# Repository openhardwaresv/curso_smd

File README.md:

Sensorino - Iniciandote con Componentes de Montaje Superficial
================================================================

Sensorino es una tableta electrónica programable compatible con
Arduino Leonardo impulsada por la comunidad OpenHardware.SV diseñada
en colaboración por TeUbi.co y ALSW para enseñar los fundamentos
básicos sobre el diseño de tabletas electrónicas haciendo uso de
componentes de montaje superficial.

La tableta es basada en el microcontrolador ATMega32u4 y contiene
el bootloader de Leonardo, pero además incluye sensores y LEDs
indicadores por lo que no requiere de componentes externos más que
una fuente de alimentación una vez programada.

Actualmente la tableta tiene la posibilidad de armarse utilizando el
sensor de gestos APDS-9960 o el inclinómetro sencillo RPI-1031. Estos
sensores permiten implementar aplicaciones muy sencillas que pueden
fácilmente ser demostradas con LEDs incluídos.

Al estar basada en Leonardo la tableta también permite utilizarse como
dispositivo de entrada (teclado o mouse) con lo que se le pueden dar
aplicaciones sumamente interesantes de interacción con computador.

Esta es una tableta didáctica diseñada con la idea de aprender las bases
del diseño utilizando componentes de montaje superficial por lo que se
incluye el mismo diseño eléctrico y de PCB en distintas etapas del
diseño que facilitan y sirven como guía de los productos esperados.

Últimas adiciones
=================

+ Agregado esquemá eléctrico

Costo/Lista de Materiales
=========================

Revisar archivo adjunto BOM.csv.

Pre-requisitos/Requerimientos
=============================

En función del diseño que quieras modificar puedes encontrar las fuentes
en distintas etapas. Sin embargo para seguir todo el proceso desde cero
necesitas cumplir los siguientes requerimientos:

Software:

* EAGLE Layout editor.
* IDE Arduino.
* GIT (para guardar tus avances)

Herramientas requeridas:

* Pistola de calor de temperatura y flujo regulable (Se recomienda Sparkfun 303D)
* Tercera mano
* Pinza curvada auto-blocante anti-estática
* Espátula plástica o tarjeta de vinil (para aplicar la pasta)
* Pasta para soldar libre de plomo

Construcción y uso
==================

Revisar directorio "Documentación"

Carpetas
========
* *doc*: Utiliza esta carpeta para ingresar toda la documentación que consideres
necesaria para tu proyecto. De preferencia utiliza formatos libres como "ODF"
o simples archivos de texto, si puedes crear una página web en HTML recuerda
renombrar el archivo principal como "index.html" para que pueda ser accedido
fácilmente en caso de que alguien copie esta carpeta en un servidor web.
* *src*: Coloca en esta carpeta todos los archivos de código fuente del software
de control de tu proyecto Open Hardware. Si utilizas un IDE como Eclipse o Arduino
copia dentro de src la carpeta del proyecto.
* *dsn* / *diseño*: En esta carpeta coloca todos los archivos para el diseño de tu
proyecto.
  +  *main*: Coloca en esta carpeta los archivos de diseño original que pueden
incluir, pero no limitarse a: Dibujos 2D, diseños 3D, archivos CAD, bibliotecas
de componentes, dibujos técnicos adicionales.
  +  *aux*: Coloca en esta carpeta los archivos de diseño auxiliares que ayuden
a construir tu proyecto. Los archivos de diseño secundario pueden incluír diseños
2D o 3D en formato de intercambio, dibujos técnicos adicionales, formatos listos
para manufactura, artes gráficos adicionales.
* *extra*: Esta carpeta es libre, aquí puedes colocar otros archivos que se
puedan requerir para hacer funcionar o construir tu proyecto. Un ejemplo de ello
puede ser un driver controlador de un dispositivo específico o vínculos a software
relevante, fotografías o videos.

Excepción de responsabilidades
==============================

Es recomendable que incluyas un texto como el siguiente en tus proyectos:

> El presente proyecto se comparte "tal cual" con el único objetivo de que sea útil.
El/los creadores del presente hardware y su software asociado no pueden garantizar su
correcto funcionamiento bajo ninguna circunstancia. El/Los autor/es de este proyecto
no podrá/n hacerse responsable/s de cualquier pérdida de carácter material, personal o
económico a su persona o terceros derivados de la utilización del mismo. Este proyecto
no deberá ser utilizado bajo ninguna circustancia en sistemas de carácter crítico
o sistemas de los cuales dependan vidas de personas de manera directa o indirecta.

Licenciamiento
==============

Agrega aquí la licencia que utilizas en el código fuente de tu proyecto, adicionalmente
agradeceríamos si colocas la nota de atribución de la plantilla al final.

> La plantilla de este README.md ha sido desarrollada por la comunidad openhardware.sv
con el objetivo de facilitar la documentación de proyectos. Esta plantilla está protegida
bajo la licencia CC BY, puedes modificarla y redistribuirla manteniendo esta nota de

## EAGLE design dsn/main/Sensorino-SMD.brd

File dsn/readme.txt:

Archivos de diseño
==================

Encuentra los archivos de diseño de Sensorino en esta carpeta.

Archivos de diseño principal:

* main\Sensorino.sch : Archivo fuente del diagráma eléctrico para Eagle.
* main\Sensorino.brd : Archivo fuente de la tableta impresa para Eagle.

Archivos de diseño auxiliar:
* main\Sensorino_sch_print.pdf : PDF para impresión del diagrama eléctrico
* main\PAD_COMBINADO.jpg : Pad combinado para ambos sensores.

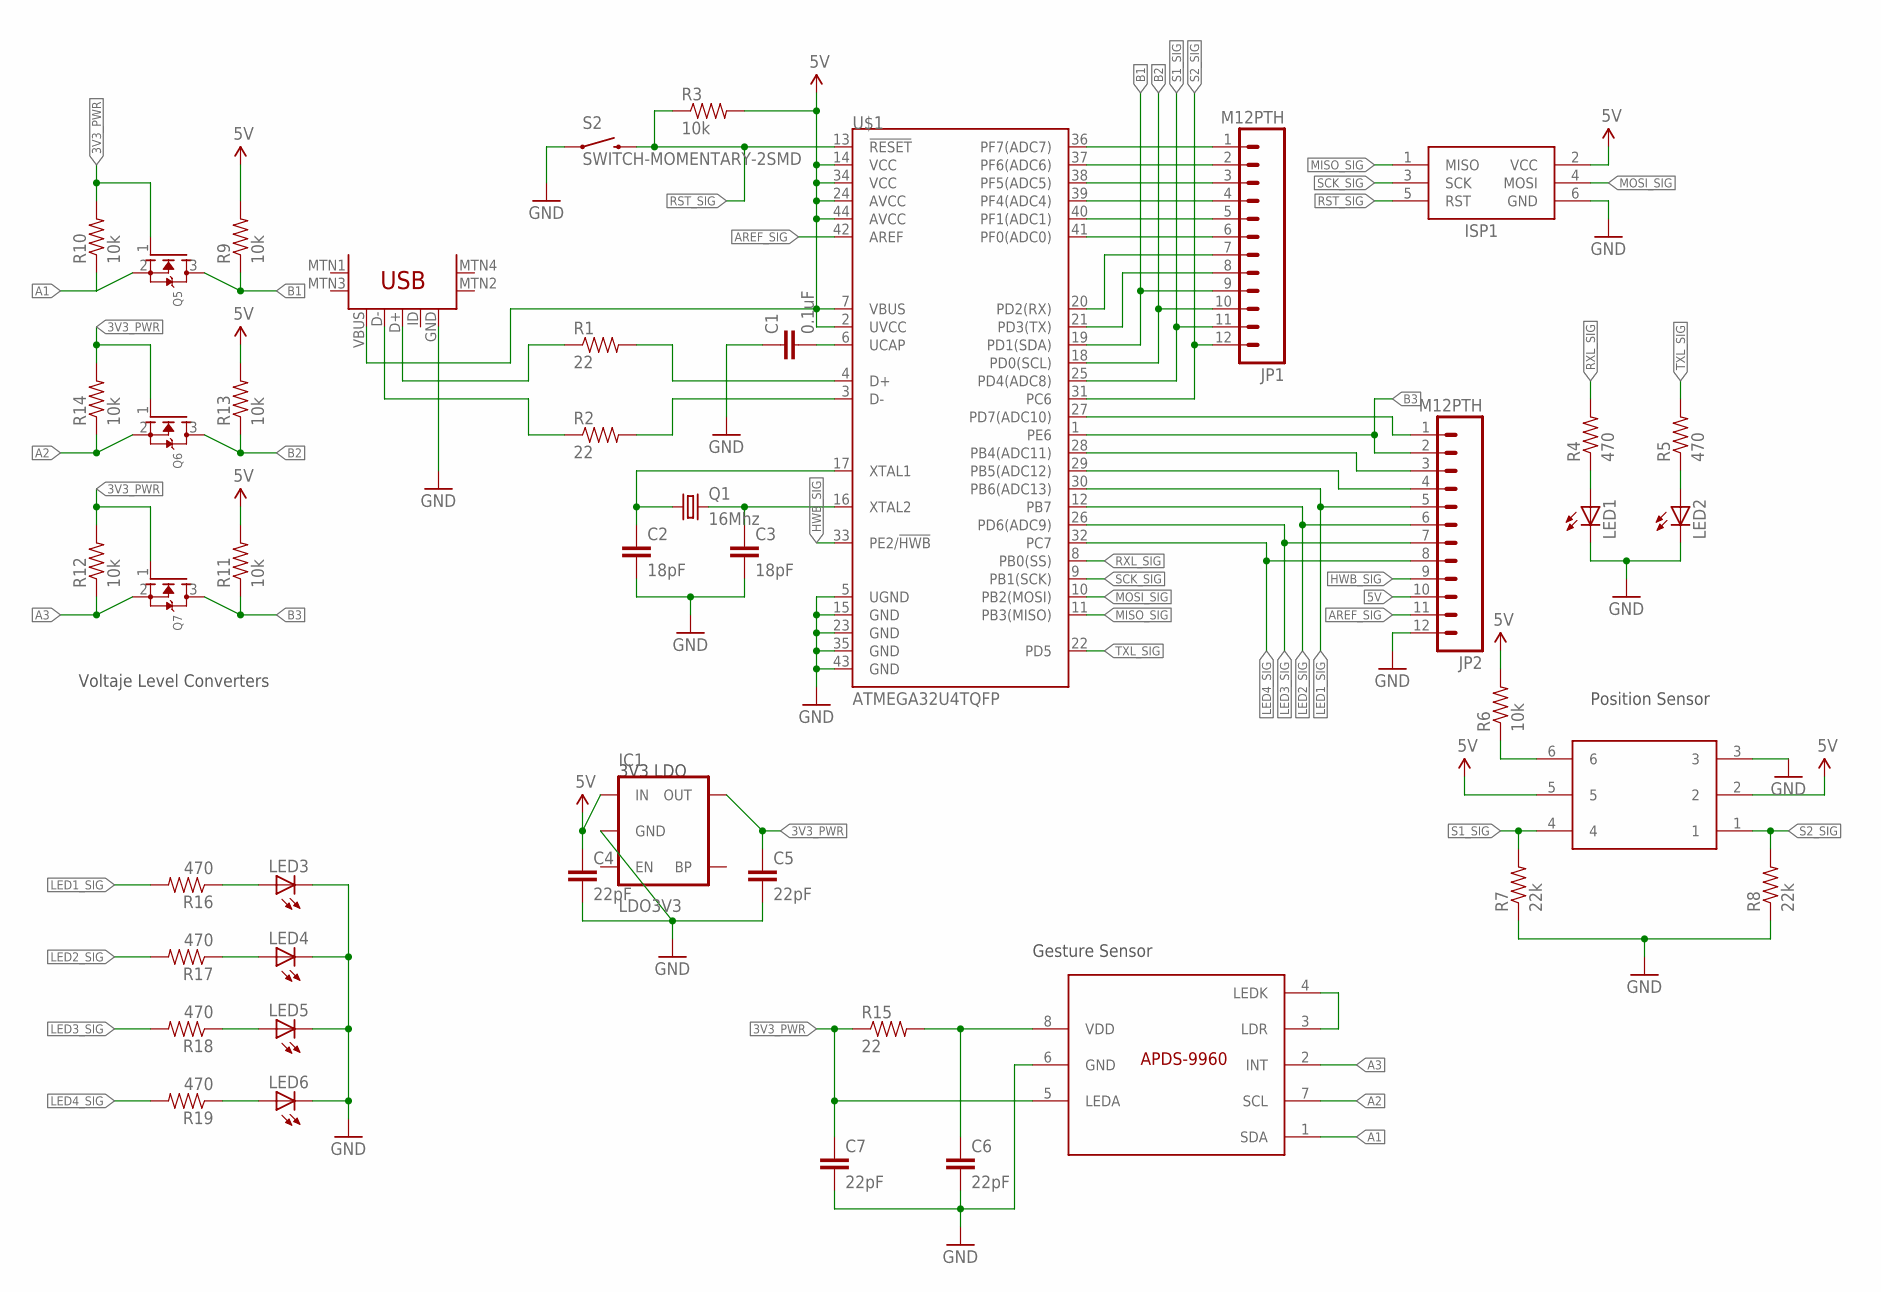
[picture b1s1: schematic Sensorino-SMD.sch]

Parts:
C1: 0.1uF; 0805
C2, C3: 18pF; 0805
C4, C5, C6, C7: 22pF; 0805
IC1: LDO3V3; SOT23-5
ISP1: AVRISP-6; AVRISP
JP1, JP2: M12PTH; 1X12
LED1, LED2, LED3, LED4, LED5, LED6: LED-WHITE; LED-1206
Q1: 16Mhz; CTS406
Q5, Q6, Q7: MOSFET-NREFLOW; SOT23
R1, R2, R15: 22; 0805
R3, R6, R9, R10, R11, R12, R13, R14: 10k; 0805
R4, R5, R16, R17, R18, R19: 470; 0805
R7, R8: 22k; 0805
S2: SWITCH-MOMENTARY-2SMD; TACTILE_SWITCH_SMD
U$1: ATMEGA32U4TQFP; SPARKFUN-DIGITALIC_TQFP44
U$2: USB-MINIB-5PIN; USB-MINIB
U$3: RPI-1031
U$4: APDS-9960

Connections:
3V3_PWR: C5.1, C7.1, IC1.5 (OUT), Q5.1 (G), Q6.1 (G), Q7.1 (G), R10.2, R12.2, R14.2, R15.1, U$4.5 (LEDA)
5V: C4.1, IC1.1 (IN), ISP1.2 (VCC), JP2.10, R3.2, R6.2, R9.2, R11.2, R13.2, U$1.2 (UVCC), U$1.7 (VBUS), U$1.14 (VCC), U$1.24 (AVCC), U$1.34 (VCC), U$1.44 (AVCC), U$2.VBUS, U$3.2, U$3.5
A1: Q5.2 (S), R10.1, U$4.1 (SDA)
A2: Q6.2 (S), R14.1, U$4.7 (SCL)
A3: Q7.2 (S), R12.1, U$4.2 (INT)
AREF_SIG: JP2.11, U$1.42 (AREF)
B1: JP1.9, Q5.3 (D), R9.1, U$1.19 (PD1(SDA))
B2: JP1.10, Q6.3 (D), R13.1, U$1.18 (PD0(SCL))
B3: JP2.2, Q7.3 (D), R11.1, U$1.1 (PE6)
D_USBD+: R2.1, U$2.D-
D_USBD-: R1.1, U$2.D+
D_USBRD+: R2.2, U$1.3 (D-)
D_USBRD-: R1.2, U$1.4 (D+)
GND: C1.1, C2.2, C3.2, C4.2, C5.2, C6.2, C7.2, IC1.2 (GND), ISP1.6 (GND), JP2.12, LED1.C, LED2.C, LED3.C, LED4.C, LED5.C, LED6.C, R7.1, R8.1, S2.1, U$1.5 (UGND), U$1.15 (GND), U$1.23 (GND), U$1.35 (GND), U$1.43 (GND), U$2.GND, U$3.3, U$4.6 (GND)
HWB_SIG: JP2.9, U$1.33 (PE2/!HWB)
LED1_SIG: JP2.5, R16.2, U$1.30 (PB6(ADC13))
LED2_SIG: JP2.6, R17.2, U$1.12 (PB7)
LED3_SIG: JP2.7, R18.2, U$1.26 (PD6(ADC9))
LED4_SIG: JP2.8, R19.2, U$1.32 (PC7)
MISO_SIG: ISP1.1 (MISO), U$1.11 (PB3(MISO))
MOSI_SIG: ISP1.4 (MOSI), U$1.10 (PB2(MOSI))
unnamed: JP2.1, U$1.27 (PD7(ADC10))
unnamed: C1.2, U$1.6 (UCAP)
unnamed: C3.1, Q1.3 (2), U$1.16 (XTAL2)
unnamed: C2.1, Q1.1, U$1.17 (XTAL1)
unnamed: LED3.A, R16.1
unnamed: JP2.3, U$1.28 (PB4(ADC11))
unnamed: LED1.A, R4.1
unnamed: LED2.A, R5.1
unnamed: JP1.1, U$1.36 (PF7(ADC7))
unnamed: JP1.2, U$1.37 (PF6(ADC6))
unnamed: JP1.3, U$1.38 (PF5(ADC5))
unnamed: JP1.4, U$1.39 (PF4(ADC4))
unnamed: JP1.5, U$1.40 (PF1(ADC1))
unnamed: JP1.6, U$1.41 (PF0(ADC0))
unnamed: JP1.7, U$1.20 (PD2(RX))
unnamed: JP1.8, U$1.21 (PD3(TX))
unnamed: LED4.A, R17.1
unnamed: LED5.A, R18.1
unnamed: LED6.A, R19.1
unnamed: JP2.4, U$1.29 (PB5(ADC12))
unnamed: R6.1, U$3.6
unnamed: U$4.3 (LDR), U$4.4 (LEDK)
unnamed: C6.1, R15.2, U$4.8 (VDD)
RST_SIG: ISP1.5 (RST), R3.1, S2.3 (2), U$1.13 (!RESET)
RXL_SIG: R4.2, U$1.8 (PB0(SS))
S1_SIG: JP1.11, R7.2, U$1.25 (PD4(ADC8)), U$3.4
S2_SIG: JP1.12, R8.2, U$1.31 (PC6), U$3.1
SCK_SIG: ISP1.3 (SCK), U$1.9 (PB1(SCK))
TXL_SIG: R5.2, U$1.22 (PD5)

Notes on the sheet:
Voltaje Level Converters
3V3 LDO
Gesture Sensor
Position Sensor

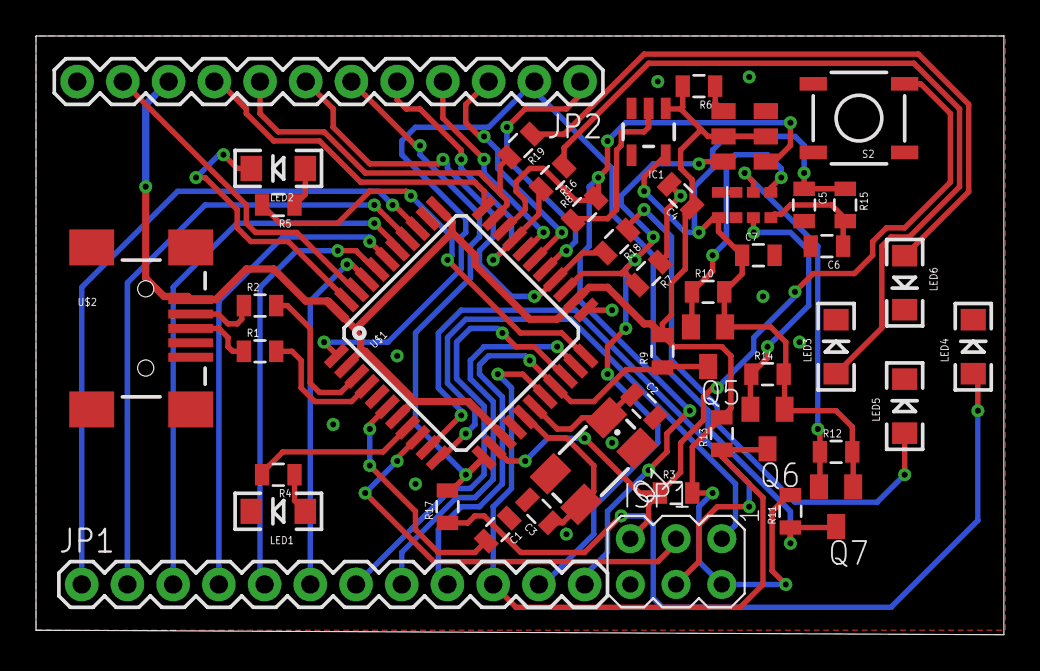
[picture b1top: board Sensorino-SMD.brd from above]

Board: 2 copper layers, 53.8 x 33.3 mm, 45 parts (0 on the bottom side), 50 nets.

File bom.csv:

Part,Value,Device,Package,Description,PROD_ID,VALUE
C1,0.1uF,0.1UF-50V-20%(PTH)KIT-EZ,CAP-PTH-SMALL-KIT,CAP-08370,CAP-08370,
C2,18pF,0.1UF-50V-20%(PTH)KIT-EZ,CAP-PTH-SMALL-KIT,CAP-08370,CAP-08370,
C3,18pF,0.1UF-50V-20%(PTH)KIT-EZ,CAP-PTH-SMALL-KIT,CAP-08370,CAP-08370,
C4,22pF,0.1UF-50V-20%(PTH)KIT-EZ,CAP-PTH-SMALL-KIT,CAP-08370,CAP-08370,
C5,22pF,0.1UF-50V-20%(PTH)KIT-EZ,CAP-PTH-SMALL-KIT,CAP-08370,CAP-08370,
C6,22pF,0.1UF-50V-20%(PTH)KIT-EZ,CAP-PTH-SMALL-KIT,CAP-08370,CAP-08370,
C7,22pF,0.1UF-50V-20%(PTH)KIT-EZ,CAP-PTH-SMALL-KIT,CAP-08370,CAP-08370,
IC1,LDO3V3,78XXL,78XXL,VOLTAGE REGULATOR,,
ISP1,AVRISP-6,AVRISP-6,AVRISP,AVR ISP HEADER,,
JP1,M12PTH,M12PTH,1X12,Header 12,,
JP2,M12PTH,M12PTH,1X12,Header 12,,
LED1,,LED5MM,LED5MM,LEDs,,
LED2,,LED5MM,LED5MM,LEDs,,
LED3,,LED5MM,LED5MM,LEDs,,
LED4,,LED5MM,LED5MM,LEDs,,
LED5,,LED5MM,LED5MM,LEDs,,
LED6,,LED5MM,LED5MM,LEDs,,
Q1,,XTAL/S,QS,CRYSTAL,,
Q2,,MOSFET-NGDS_TO220V,TO220V,N-Channel Mosfet,,
Q3,,MOSFET-NGDS_TO220V,TO220V,N-Channel Mosfet,,
Q4,,MOSFET-NGDS_TO220V,TO220V,N-Channel Mosfet,,
R1,22,RESISTORAXIAL-0.3,AXIAL-0.3,Resistor,,
R2,22,RESISTORAXIAL-0.3,AXIAL-0.3,Resistor,,
R3,10k,RESISTORAXIAL-0.3,AXIAL-0.3,Resistor,,
R4,470,RESISTORAXIAL-0.3,AXIAL-0.3,Resistor,,
R5,470,RESISTORAXIAL-0.3,AXIAL-0.3,Resistor,,
R6,10k,RESISTORAXIAL-0.3,AXIAL-0.3,Resistor,,
R7,22k,RESISTORAXIAL-0.3,AXIAL-0.3,Resistor,,
R8,22k,RESISTORAXIAL-0.3,AXIAL-0.3,Resistor,,
R9,10k,RESISTORAXIAL-0.3,AXIAL-0.3,Resistor,,
R10,10k,RESISTORAXIAL-0.3,AXIAL-0.3,Resistor,,
R11,10k,RESISTORAXIAL-0.3,AXIAL-0.3,Resistor,,
R12,10k,RESISTORAXIAL-0.3,AXIAL-0.3,Resistor,,
R13,10k,RESISTORAXIAL-0.3,AXIAL-0.3,Resistor,,
R14,10k,RESISTORAXIAL-0.3,AXIAL-0.3,Resistor,,
R15,22,RESISTORAXIAL-0.3,AXIAL-0.3,Resistor,,
R16,470,RESISTORAXIAL-0.3,AXIAL-0.3,Resistor,,
R17,470,RESISTORAXIAL-0.3,AXIAL-0.3,Resistor,,
R18,470,RESISTORAXIAL-0.3,AXIAL-0.3,Resistor,,
R19,470,RESISTORAXIAL-0.3,AXIAL-0.3,Resistor,,
S1,,TAC_SWITCHPTH,TACTILE-PTH,Momentary Switch,,
U$1,ATMEGA32U4TQFP,ATMEGA32U4TQFP,SPARKFUN-DIGITALIC_TQFP44,Atmel 44-pin 8-bit Microcontroller with 32KBytes of ISP Flash and USB Controller -----,,
U$2,USBPTH,USBPTH,USB-B-PTH,USB Connectors,CONN-08278,USB-B
U$3,RPI-1031,RPI-1031,RPI-1031,,,
U$4,APDS-9960,APDS-9960,APDS-9960,,,

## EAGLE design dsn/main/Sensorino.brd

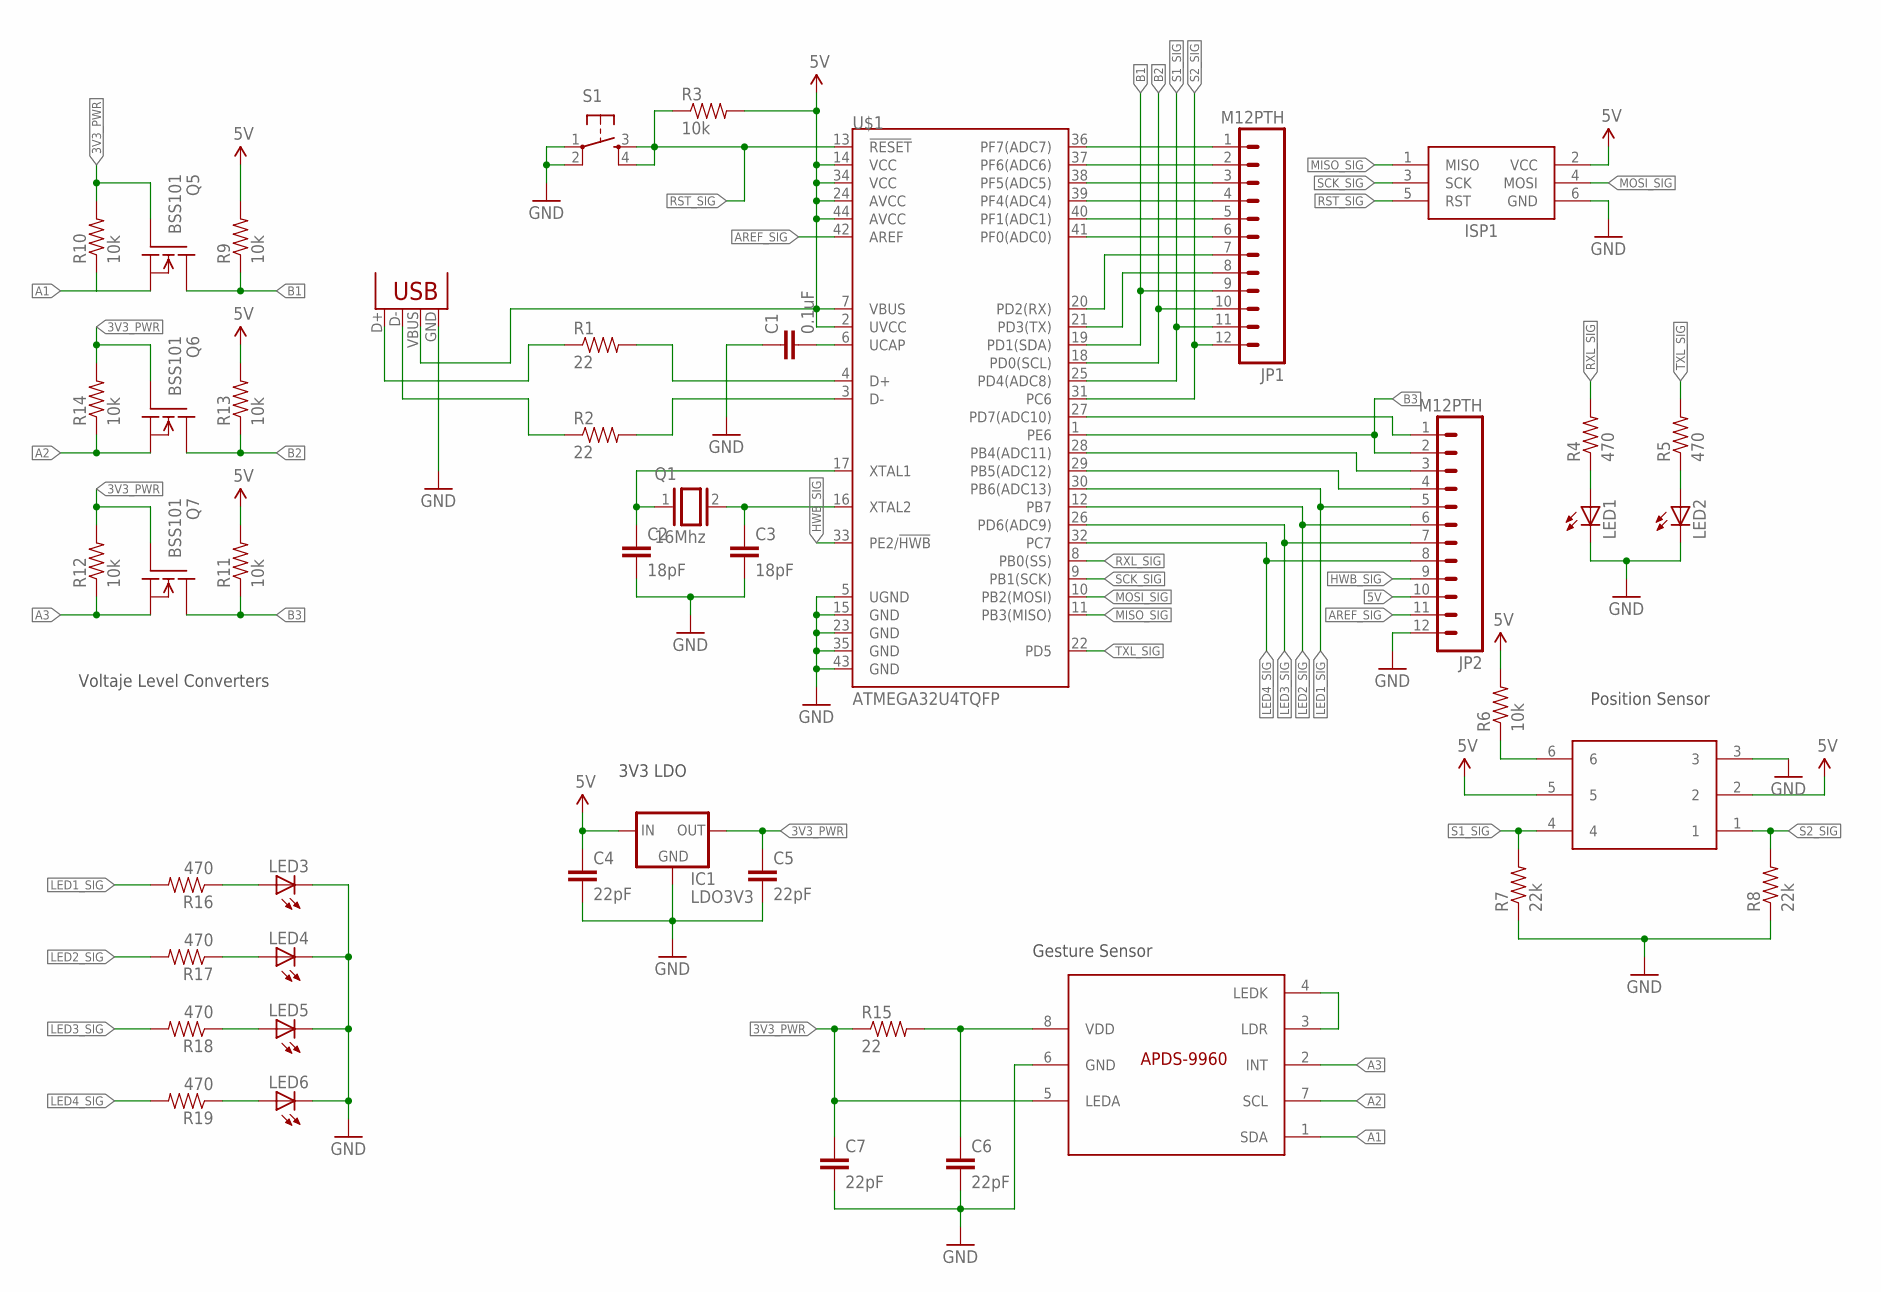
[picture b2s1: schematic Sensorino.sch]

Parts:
C1: 0.1uF; CAP-PTH-SMALL-KIT
C2, C3: 18pF; CAP-PTH-SMALL-KIT
C4, C5, C6, C7: 22pF; CAP-PTH-SMALL-KIT
IC1: LDO3V3; 78XXL
ISP1: AVRISP-6; AVRISP
JP1, JP2: M12PTH; 1X12
LED1, LED2, LED3, LED4, LED5, LED6: LED5MM
Q1: 16Mhz; QS
Q5, Q6, Q7: BSS101; TO92
R1, R2, R15: 22; AXIAL-0.3
R3, R6, R9, R10, R11, R12, R13, R14: 10k; AXIAL-0.3
R4, R5, R16, R17, R18, R19: 470; AXIAL-0.3
R7, R8: 22k; AXIAL-0.3
S1: TAC_SWITCHPTH; TACTILE-PTH
U$1: ATMEGA32U4TQFP; SPARKFUN-DIGITALIC_TQFP44
U$2: USBPTH; USB-B-PTH
U$3: RPI-1031
U$4: APDS-9960

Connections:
3V3_PWR: C5.1, C7.1, IC1.OUT, Q5.2 (G), Q6.2 (G), Q7.2 (G), R10.P$2 (2), R12.P$2 (2), R14.P$2 (2), R15.P$1 (1), U$4.5 (LEDA)
5V: C4.1, IC1.IN, ISP1.2 (VCC), JP2.10, R3.P$2 (2), R6.P$2 (2), R9.P$2 (2), R11.P$2 (2), R13.P$2 (2), U$1.2 (UVCC), U$1.7 (VBUS), U$1.14 (VCC), U$1.24 (AVCC), U$1.34 (VCC), U$1.44 (AVCC), U$2.VBUS, U$3.2, U$3.5
A1: Q5.1 (S), R10.P$1 (1), U$4.1 (SDA)
A2: Q6.1 (S), R14.P$1 (1), U$4.7 (SCL)
A3: Q7.1 (S), R12.P$1 (1), U$4.2 (INT)
AREF_SIG: JP2.11, U$1.42 (AREF)
B1: JP1.9, Q5.3 (D), R9.P$1 (1), U$1.19 (PD1(SDA))
B2: JP1.10, Q6.3 (D), R13.P$1 (1), U$1.18 (PD0(SCL))
B3: JP2.2, Q7.3 (D), R11.P$1 (1), U$1.1 (PE6)
GND: C1.1, C2.2, C3.2, C4.2, C5.2, C6.2, C7.2, IC1.GND, ISP1.6 (GND), JP2.12, LED1.K (C), LED2.K (C), LED3.K (C), LED4.K (C), LED5.K (C), LED6.K (C), R7.P$1 (1), R8.P$1 (1), S1.1, S1.2, U$1.5 (UGND), U$1.15 (GND), U$1.23 (GND), U$1.35 (GND), U$1.43 (GND), U$2.GND, U$3.3, U$4.6 (GND)
HWB_SIG: JP2.9, U$1.33 (PE2/!HWB)
LED1_SIG: JP2.5, R16.P$2 (2), U$1.30 (PB6(ADC13))
LED2_SIG: JP2.6, R17.P$2 (2), U$1.12 (PB7)
LED3_SIG: JP2.7, R18.P$2 (2), U$1.26 (PD6(ADC9))
LED4_SIG: JP2.8, R19.P$2 (2), U$1.32 (PC7)
MISO_SIG: ISP1.1 (MISO), U$1.11 (PB3(MISO))
MOSI_SIG: ISP1.4 (MOSI), U$1.10 (PB2(MOSI))
unnamed: R2.P$2 (2), U$1.3 (D-)
unnamed: R1.P$2 (2), U$1.4 (D+)
unnamed: R1.P$1 (1), U$2.D+
unnamed: R2.P$1 (1), U$2.D-
unnamed: JP2.1, U$1.27 (PD7(ADC10))
unnamed: C1.2, U$1.6 (UCAP)
unnamed: C3.1, Q1.2, U$1.16 (XTAL2)
unnamed: C2.1, Q1.1, U$1.17 (XTAL1)
unnamed: LED3.A, R16.P$1 (1)
unnamed: JP2.3, U$1.28 (PB4(ADC11))
unnamed: LED1.A, R4.P$1 (1)
unnamed: LED2.A, R5.P$1 (1)
unnamed: JP1.1, U$1.36 (PF7(ADC7))
unnamed: JP1.2, U$1.37 (PF6(ADC6))
unnamed: JP1.3, U$1.38 (PF5(ADC5))
unnamed: JP1.4, U$1.39 (PF4(ADC4))
unnamed: JP1.5, U$1.40 (PF1(ADC1))
unnamed: JP1.6, U$1.41 (PF0(ADC0))
unnamed: JP1.7, U$1.20 (PD2(RX))
unnamed: JP1.8, U$1.21 (PD3(TX))
unnamed: LED4.A, R17.P$1 (1)
unnamed: LED5.A, R18.P$1 (1)
unnamed: LED6.A, R19.P$1 (1)
unnamed: JP2.4, U$1.29 (PB5(ADC12))
unnamed: R6.P$1 (1), U$3.6
unnamed: U$4.3 (LDR), U$4.4 (LEDK)
unnamed: C6.1, R15.P$2 (2), U$4.8 (VDD)
RST_SIG: ISP1.5 (RST), R3.P$1 (1), S1.3, S1.4, U$1.13 (!RESET)
RXL_SIG: R4.P$2 (2), U$1.8 (PB0(SS))
S1_SIG: JP1.11, R7.P$2 (2), U$1.25 (PD4(ADC8)), U$3.4
S2_SIG: JP1.12, R8.P$2 (2), U$1.31 (PC6), U$3.1
SCK_SIG: ISP1.3 (SCK), U$1.9 (PB1(SCK))
TXL_SIG: R5.P$2 (2), U$1.22 (PD5)

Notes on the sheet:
Voltaje Level Converters
3V3 LDO
Gesture Sensor
Position Sensor

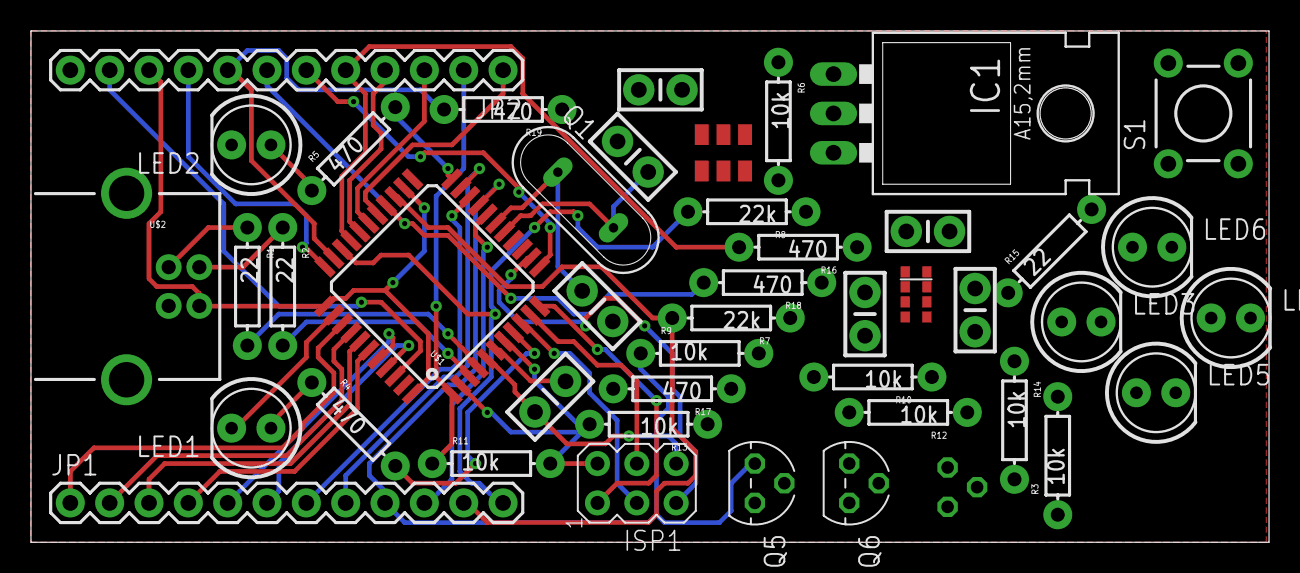
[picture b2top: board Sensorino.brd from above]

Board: 2 copper layers, 79.9 x 33.0 mm, 45 parts (1 on the bottom side), 50 nets.

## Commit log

2015-05-19 Added datasheets
2015-05-19 Added docu
2015-05-19 Values corrected for R7 & R8
2015-05-19 Added indicator LEDs
2015-05-19 Reestructurado formato de plantilla.
2015-05-19 Added readme
2015-05-19 Name fixed
2015-05-19 Added PTH render
2015-05-19 Mosfet changed to a more-acceptable model
2015-05-19 Modified PTH PCB Layout
2015-05-26 Added SMD version

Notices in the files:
dsn/main/Sensorino-SMD.sch:
Released under CC-BY-SA 3.0
parts and their libraries:
SparkFun-DigitalIC: Licensing: CC v3.0 Share-Alike You are welcome to use this library for commercial purposes.
